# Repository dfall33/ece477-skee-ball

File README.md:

# Electronic Skee Ball Machine

## Overview 

This repository contains the source code for the Electronic Skee Ball machine project. This project was created as a senior capstone design project for Purdue University's ECE47700 
course in Spring 2025. 
This project was created by: 
* **Andrew Cali (*Hardware Lead*)**
* **David Fall (*Team Lead*)**
* **Jennifer Ferguson (*Software Lead*)**
* **Madeline Flanagan (*Systems Lead*)**

all of whom are (or were at the time) computer engineering students at Purdue University. 

## Repository Structure
This repository is divided into numerous discrete sections. 
* **src**: This folder contains the embedded C source code for the project. The software in this directory is the final software that was run on the hardware (specifically, on the STM32F091RCT6 MCU that was used in this project). 
* **micropython**: This directory contains some micropython code that was used during early prototyping done on an ESP32 Feather v2 development board. This development board (or any type of ESP32) was not used in the final design of the project. None of the software in this directory was used in the final design of the project.
* **docs**: This folder contains any and all technical documentation for the project. This includes a product overview, functional specification, etc.
* **hardware**: This folder contains the KiCAD project files for the hardware of the project. This includes the schematic and PCB layout. 
* **packaging**: This folder contains the CAD files for the packaging of the project. This includes the design files for the enclosure and any other packaging components.

## Additional Documentation 

Any and all technical documentation, including a product overview, functional specification, etc., can be found in the `docs` folder in this repository.

## Demonstration Video
A demonstration video of the project can be found at the following link: [Electronic Skee Ball Machine Demonstration Video](https://youtu.be/028JnDdOcIg). This same video is available in MP4 format in the A14 - Project Archive zip file in this repository.

## Hardware Design
The hardware of the project, including the schematic and PCB layout, is designed using KiCAD. The KiCAD project files can be found in the `hardware` folder. 

## Packaging Design 
The packaging for the product hardware and user interface was designed using a variety of softwares. The main components of the packaging design were designed using CAD. Relevant CAD files are contained in the `packaging` folder in this repository. 

Various resources at Purdue University were used to create the packaging. These include but are not limited to university-provided 3D printers and university-owned woodworking tools.

## Reusability 
The software contained in this repository was designed specifically for the hardware of this project. It is not intended for reuse on alternative hardware configurations. However, should one order the exact PCB that was designed for this project and incorporate the components listed in the BOM, the software should work as intended.

## Contact Information
At the time of reading this, it is possible that the team members have graduated from Purdue University, meaning that they may not be reachable at their Purdue email addresses. For any questions or comments, please contact David Fall at his personal email address 
[david.c.fall33@gmail.com](mailto:david.c.fall33@gmail.com).

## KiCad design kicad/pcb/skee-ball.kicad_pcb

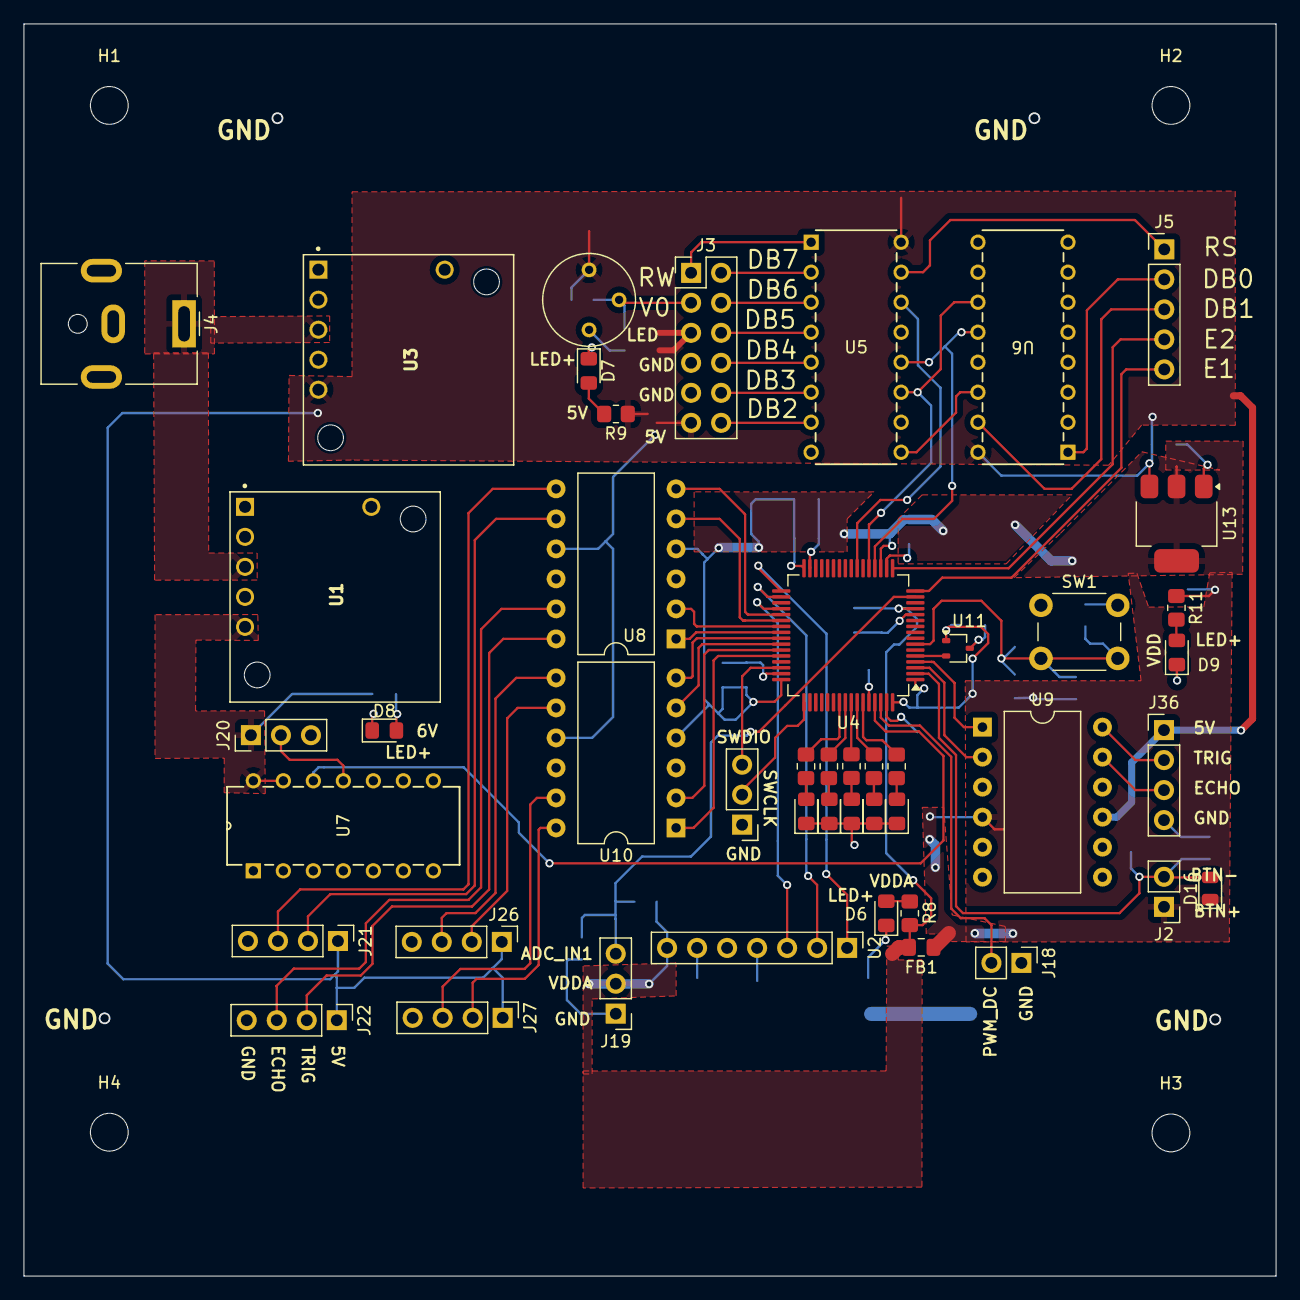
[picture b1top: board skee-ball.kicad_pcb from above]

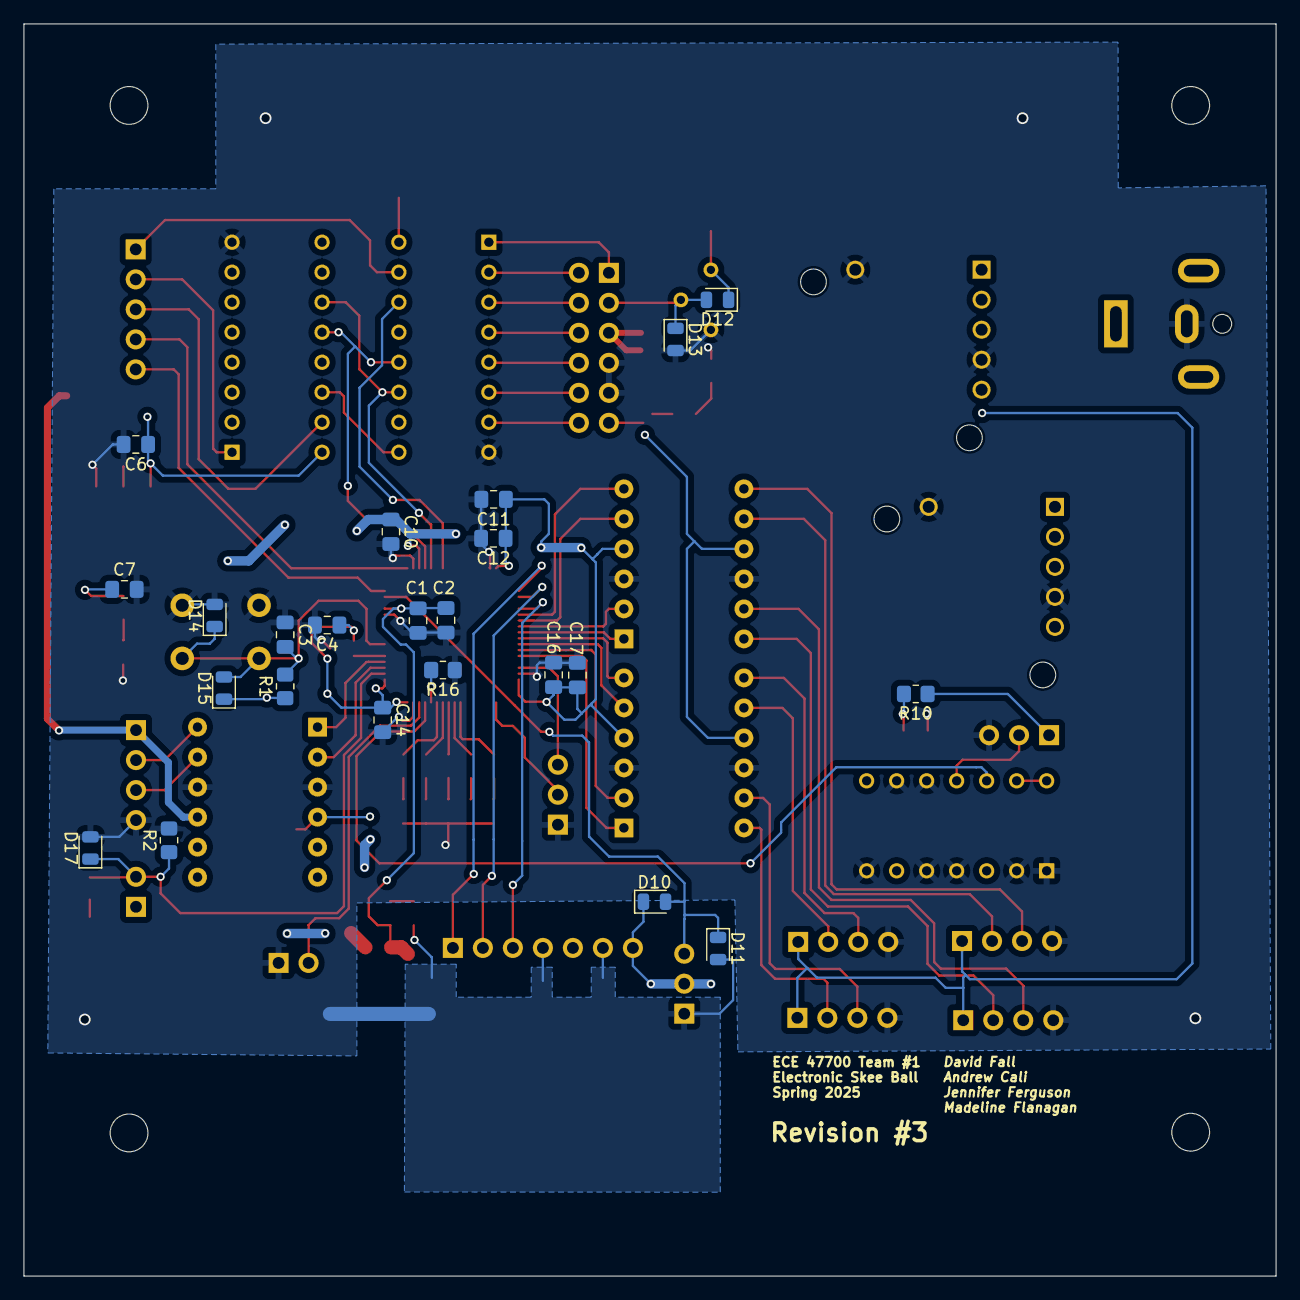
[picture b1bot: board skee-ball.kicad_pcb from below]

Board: 2 copper layers, 106.0 x 106.0 mm, 73 parts (23 on the bottom side), 70 nets.

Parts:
C1: 10nF; C_0805_2012Metric_Pad1.18x1.45mm_HandSolder
C2: 1uF; C_0805_2012Metric_Pad1.18x1.45mm_HandSolder
C3, C4, C6, C10, C12, C14, C16: 100nF; C_0805_2012Metric_Pad1.18x1.45mm_HandSolder
C7: 10uF; C_0805_2012Metric_Pad1.18x1.45mm_HandSolder
C11, C17: 4.7uF; C_0805_2012Metric_Pad1.18x1.45mm_HandSolder
D1, D2, D3, D4, D5, D6, D7, D8, D9: LED; LED_0805_2012Metric_Pad1.15x1.40mm_HandSolder
D10, D11, D12, D13, D14, D15, D16, D17: D_Schottky; D_0805_2012Metric
FB1: FerriteBead; C_0805_2012Metric_Pad1.18x1.45mm_HandSolder
H1, H2, H3, H4: MountingHole; MountingHole_3.2mm_M3
J2: EXTERNAL_BUTTON; PinHeader_1x02_P2.54mm_Vertical
J3: NHD_CONN1; PinHeader_2x06_P2.54mm_Vertical
J4: Barrel_Jack; BarrelJack_CUI_PJ-063AH_Horizontal
J5: NHD_CONN2; PinHeader_1x05_P2.54mm_Vertical
J13: HEADER; PinHeader_1x03_P2.54mm_Vertical
J18: DC_DRIVER; PinHeader_1x02_P2.54mm_Vertical
J19: JOYSTICK; PinHeader_1x03_P2.54mm_Vertical
J20: SERVO; PinHeader_1x03_P2.54mm_Vertical
J21: US0; PinHeader_1x04_P2.54mm_Vertical
J22: US1; PinHeader_1x04_P2.54mm_Vertical
J26: US2; PinHeader_1x04_P2.54mm_Vertical
J27: US3; PinHeader_1x04_P2.54mm_Vertical
J36: US4; PinHeader_1x04_P2.54mm_Vertical
R1, R2: 10k; R_0805_2012Metric_Pad1.20x1.40mm_HandSolder
R3, R4, R5, R6, R7, R8, R11: 150; R_0805_2012Metric_Pad1.20x1.40mm_HandSolder
R9: 200; R_0805_2012Metric_Pad1.20x1.40mm_HandSolder
R10: 300; R_0805_2012Metric_Pad1.20x1.40mm_HandSolder
R16: 2200; R_0805_2012Metric_Pad1.20x1.40mm_HandSolder
RV1: 10k; Potentiometer_Bourns_3339P_Vertical
SW1: SW_Push; SW_PUSH_6mm
U1: D24V22F6; XDCR_12V_2.2A_STEP-DOWN_D24V22F12
U2: MAX98357A; PinHeader_1x07_P2.54mm_Vertical
U3: D24V22F5; XDCR_12V_2.2A_STEP-DOWN_D24V22F12
U4: STM32F091RCTx; LQFP-64_10x10mm_P0.5mm
U5, U6: 74HC595; SOT38-4_NXP
U7: 74LS08; N14
U8, U9, U10: DIP-12_W10.16mm
U11: MAX7375AXR805; SOT-323_SC-70
U13: LD1117S33TR_SOT223; SOT-223-3_TabPin2

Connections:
+5V: C6.1, D12.1 (K), J3.5, J3.11, J21.1, J22.1, J26.1, J27.1, J36.1, R9.1, RV1.1, U3.5 (VOUT), U5.16 (VCC), U6.16 (VCC), U8.9 (HV), U9.9 (HV), U10.9 (HV), U13.3 (VI)
+6V: J20.1, R10.1, U1.5 (VOUT), U7.13, U7.14 (VCC)
+24V: J4.1, U1.3 (VIN), U3.3 (VIN)
/BOOT0: R16.2, U4.60 (PF11)
ADC_IN1: D10.2 (A), D11.1 (K), J19.3, U4.15 (PA1)
BUTTON_IN: D16.2 (A), D17.1 (K), J2.2, R2.1, U4.2 (PC13)
EXTERNAL_CLK: U4.5 (PF0), U11.2 (CLOCK)
GND: C1.2, C2.2, C3.1, C4.2, C6.2, C7.2, C10.2, C11.2, C12.2, C14.2, C16.2, C17.2, D1.1 (K), D2.1 (K), D3.1 (K), D4.1 (K), D5.1 (K), D6.1 (K), D7.1 (K), D8.1 (K), D9.1 (K), D11.2 (A), D13.2 (A), D14.2 (A), D17.2 (A), J3.7, J3.9, J4.2, J13.1, J18.1, J19.1, J20.3, J21.4, J22.4, J26.4, J27.4, J36.4, R2.2, R16.1, RV1.3, SW1.1, U1.4 (GND), U1.6 (GND), U2.4 (GAIN_SLOT), U2.6 (GND), U3.4 (GND), U3.6 (GND), U4.12 (VSSA), U4.18 (VSS), U4.31 (VSS), U4.47 (VSS), U4.63 (VSS), U5.8 (GND), U6.8 (GND), U7.1, U7.2, U7.4, U7.5, U7.7 (GND), U7.9, U7.10, U8.3 (GND), U8.10 (GND), U9.3 (GND), U9.10 (GND), U10.3 (GND), U10.10 (GND), U11.3 (GND), U13.1 (GND)
NHD_DB0: J5.2, U6.1 (QB)
NHD_DB1: J5.3, U6.15 (QA)
NHD_DB2: J3.12, U5.7 (QH)
NHD_DB3: J3.10, U5.6 (QG)
NHD_DB4: J3.8, U5.5 (QF)
NHD_DB5: J3.6, U5.4 (QE)
NHD_DB6: J3.4, U5.3 (QD)
NHD_DB7: J3.2, U5.2 (QC)
NHD_E1: J5.5, U4.16 (PA2)
NHD_E2: J5.4, U4.17 (PA3)
NHD_RS: J5.1, U5.15 (QA)
NHD_RW: J3.1, U5.1 (QB)
NHD_V0: D12.2 (A), D13.1 (K), J3.3, RV1.2
NRST: C3.2, D14.1 (K), D15.2 (A), R1.2, SW1.2, U4.7 (NRST)
unnamed: D1.2 (A), R3.2
unnamed: D2.2 (A), R4.2
unnamed: D3.2 (A), R5.2
unnamed: D4.2 (A), R6.2
unnamed: D5.2 (A), R7.2
unnamed: D6.2 (A), R8.2
unnamed: D7.2 (A), R9.2
unnamed: D8.2 (A), R10.2
unnamed: D9.2 (A), R11.2
PB3: R6.1, U4.55 (PB3)
PB4: R7.1, U4.56 (PB4)
PB5: R3.1, U4.57 (PB5)
PB6: R4.1, U4.58 (PB6)
PB7: R5.1, U4.59 (PB7)
PWM_DC: J18.2, U4.62 (PB9)
PWM_SERVO_3.3: U4.61 (PB8), U7.12
PWM_SERVO_6: J20.2, U7.11
RCLK: U4.20 (PA4), U5.12 (RCLK), U6.12 (RCLK)
SER-CHAIN: U5.9 (QH'), U6.14 (SER)
SPI1-MOSI: U4.23 (PA7), U5.14 (SER)
SPI1-SCK: U4.21 (PA5), U5.11 (SRCLK), U6.11 (SRCLK)
SPI2-MOSI(I2S_SD): U2.3 (DIN), U4.36 (PB15)
SPI2-NSS(I2S_WS): U2.1 (LRCLK), U4.33 (PB12)
SPI2-SCK(I2S_CK): U2.2 (BCLK), U4.34 (PB13)
SWCLK: J13.2, U4.49 (PA14)
SWDIO: J13.3, U4.46 (PA13)
US_ECHO0_3.3: U4.37 (PC6), U8.6 (LV1)
US_ECHO0_5: J21.3, U8.7 (HV1)
US_ECHO1_3.3: U4.39 (PC8), U8.2 (LV3)
US_ECHO1_5: J22.3, U8.11 (HV3)
US_ECHO2_3.3: U4.41 (PA8), U10.6 (LV1)
US_ECHO2_5: J26.3, U10.7 (HV1)
US_ECHO3_3.3: U4.43 (PA10), U10.2 (LV3)
US_ECHO3_5: J27.3, U10.11 (HV3)
US_ECHO4_3.3: U4.3 (PC14), U9.2 (LV3)
US_ECHO4_5: J36.3, U9.11 (HV3)
US_TRIG0_3.3: U4.38 (PC7), U8.5 (LV2)
US_TRIG0_5: J21.2, U8.8 (HV2)
US_TRIG1_3.3: U4.40 (PC9), U8.1 (LV4)
US_TRIG1_5: J22.2, U8.12 (HV4)
US_TRIG2_3.3: U4.42 (PA9), U10.5 (LV2)
US_TRIG2_5: J26.2, U10.8 (HV2)
US_TRIG3_3.3: U4.44 (PA11), U10.1 (LV4)
US_TRIG3_5: J27.2, U10.12 (HV4)
US_TRIG4_3.3: U4.4 (PC15), U9.1 (LV4)
US_TRIG4_5: J36.2, U9.12 (HV4)
VDD: C4.1, C7.1, C10.1, C11.1, C12.1, C14.1, C16.1, C17.1, D15.1 (K), D16.1 (K), FB1.1, J2.1, R1.1, R11.1, U4.1 (VBAT), U4.19 (VDD), U4.32 (VDD), U4.48 (VDDIO2), U4.64 (VDD), U8.4 (LV), U9.4 (LV), U10.4 (LV), U11.1 (V+), U13.2 (VO)
VDDA: C1.1, C2.1, D10.1 (K), FB1.2, J19.2, R8.1, U2.7 (VDD), U4.13 (VDDA)

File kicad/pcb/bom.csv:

"Reference","Value","Datasheet","Footprint","Qty","DNP"
"C1","10nF","~","Capacitor_SMD:C_0805_2012Metric_Pad1.18x1.45mm_HandSolder","1",""
"C3,C6,C10,C12,C14,C16","100nF","~","Capacitor_SMD:C_0805_2012Metric_Pad1.18x1.45mm_HandSolder","6",""
"C2","1uF","~","Capacitor_SMD:C_0805_2012Metric_Pad1.18x1.45mm_HandSolder","1",""
"C11,C17","4.7uF","~","Capacitor_SMD:C_0805_2012Metric_Pad1.18x1.45mm_HandSolder","2",""
"C7","10uF","~","Capacitor_SMD:C_0805_2012Metric_Pad1.18x1.45mm_HandSolder","1",""
"R3,R4,R5,R6,R7,R8,R11","150","~","Resistor_SMD:R_0805_2012Metric_Pad1.20x1.40mm_HandSolder","7",""
"R9","200","~","Resistor_SMD:R_0805_2012Metric_Pad1.20x1.40mm_HandSolder","1",""
"R10","300","~","Resistor_SMD:R_0805_2012Metric_Pad1.20x1.40mm_HandSolder","1",""
"R1,R2","10k","~","Resistor_SMD:R_0805_2012Metric_Pad1.20x1.40mm_HandSolder","2",""
"RV1","10k","~","Potentiometer_THT:Potentiometer_Bourns_3339P_Vertical","1",""
"U5,U6","74HC595","http://www.ti.com/lit/ds/symlink/sn74hc595.pdf","74HC595N:SOT38-4_NXP","2",""
"U7","74LS08","http://www.ti.com/lit/gpn/sn74LS08","SN74LS08N:N14","1",""
"J4","Barrel_Jack","~","Connector_BarrelJack:BarrelJack_CUI_PJ-063AH_Horizontal","1",""
"J5","Conn_01x05","~","Connector_PinHeader_2.54mm:PinHeader_1x05_P2.54mm_Vertical","1",""
"J3","Conn_02x06_Counter_Clockwise","~","Connector_PinHeader_2.54mm:PinHeader_2x06_P2.54mm_Vertical","1",""
"U3","D24V22F5","https://engineering.purdue.edu/477grp1/Files/refs/d24v22f5.pdf","12V_2.2A_STEP-DOWN_D24V22F12:XDCR_12V_2.2A_STEP-DOWN_D24V22F12","1",""
"U1","D24V22F6","https://engineering.purdue.edu/477grp1/Files/refs/d24v22f6.pdf","12V_2.2A_STEP-DOWN_D24V22F12:XDCR_12V_2.2A_STEP-DOWN_D24V22F12","1",""
"J18","DC_DRIVER","~","Connector_PinHeader_2.54mm:PinHeader_1x02_P2.54mm_Vertical","1",""
"J2","EXTERNAL_BUTTON","~","Connector_PinHeader_2.54mm:PinHeader_1x02_P2.54mm_Vertical","1",""
"FB1","FerriteBead","~","Capacitor_SMD:C_0805_2012Metric_Pad1.18x1.45mm_HandSolder","1",""
"J13","HEADER","~","Connector_PinHeader_2.54mm:PinHeader_1x03_P2.54mm_Vertical","1",""
"J19","JOYSTICK","~","Connector_PinHeader_2.54mm:PinHeader_1x03_P2.54mm_Vertical","1",""
"U13","LD1117S33TR_SOT223","http://www.st.com/st-web-ui/static/active/en/resource/techni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","Package_TO_SOT_SMD:SOT-223-3_TabPin2","1",""
"D1,D2,D3,D4,D5,D6,D7,D8,D9","LED","~","LED_SMD:LED_0805_2012Metric_Pad1.15x1.40mm_HandSolder","9",""
"U2","MAX98357A","https://www.analog.com/media/en/technical-documentation/data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","max98357A:MAX98347A_ADAFRUIT_I2S_BREAKOUT","1",""
"J20","SERVO","~","Connector_PinHeader_2.54mm:PinHeader_1x03_P2.54mm_Vertical","1",""
"U4","STM32F091RCTx","https://engineering.purdue.edu/477grp1/Files/refs/stm32f091cc.pdf","Package_QFP:LQFP-64_10x10mm_P0.5mm","1",""
"SW1","SW_Push","~","Button_Switch_THT:SW_PUSH_6mm","1",""
"J21","US0","~","Connector_PinHeader_2.54mm:PinHeader_1x04_P2.54mm_Vertical","1",""
"J22","US1","~","Connector_PinHeader_2.54mm:PinHeader_1x04_P2.54mm_Vertical","1",""
"J26","US2","~","Connector_PinHeader_2.54mm:PinHeader_1x04_P2.54mm_Vertical","1",""
"J27","US3","~","Connector_PinHeader_2.54mm:PinHeader_1x04_P2.54mm_Vertical","1",""
"J36","US4","~","Connector_PinHeader_2.54mm:PinHeader_1x04_P2.54mm_Vertical","1",""
"U8,U9,U10","~","","Package_DIP:DIP-12_W10.16mm","3",""

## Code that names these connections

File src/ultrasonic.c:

#include "ultrasonic.h"
#include "stm32f0xx.h"

void micro_wait(int);

volatile int pulse_timed_out = 0;
volatile int search_timed_out = 0;

volatile int timeout_counter = 0;

extern void led_high(int index);
extern void led_low(int index);

extern void spi_write_str(char *, int);

void time_out_pulse()
{
    pulse_timed_out = 1;
}

void time_out_hcsr04_search()
{
    spi_write_str("Time out!", 3); // Display timeout message on the display
    search_timed_out = 1;
}

uint8_t read_hcsr04(int index)
{

    switch (index)
    {
    // first sensor echo=PC6, trigger=PC7
    case 0:
        return wait_for_echo(
            GPIOC,      // port,
            GPIO_IDR_6, // idr pin
            GPIO_ODR_7  // odr pin
        );

    // second sensor echo=PC8, trigger=PC9
    case 1:
        return wait_for_echo(
            GPIOC,      // port,
            GPIO_IDR_8, // idr pin
            GPIO_ODR_9  // odr pin
        );

    // third sensor echo=PA8, trigger=PA9
    case 2:
        return wait_for_echo(
            GPIOA,      // port,
            GPIO_IDR_8, // idr pin
            GPIO_ODR_9  // odr pin
        );

    // third sensor echo=PA10, trigger=PA11
    case 3:
        return wait_for_echo(
            GPIOA,       // port,
            GPIO_IDR_10, // idr pin
            GPIO_ODR_11  // odr pin
        );

    // fifth sensor echo = PC14, trigger = PC15
    case 4:
        return wait_for_echo(
            GPIOC,       // port,
            GPIO_IDR_14, // idr pin
            GPIO_ODR_15  // odr pin
        );
    }

    return 0; 
}

void start_hcsr04_pulse_timer()
{
    TIM14->CNT = 0;
    TIM14->DIER |= TIM_DIER_UIE;
    TIM14->CR1 |= TIM_CR1_CEN;
}

void stop_hcsr04_pulse_timer()
{
    TIM14->CR1 &= ~TIM_CR1_CEN;
    TIM14->DIER &= ~TIM_DIER_UIE;
}

void start_hcsr04_search_timer()
{
    NVIC_ClearPendingIRQ(TIM15_IRQn); // Clear any pending interrupt for TIM15 before starting it
    TIM15->CNT = 0;
    TIM15->DIER |= TIM_DIER_UIE;
    TIM15->SR &= ~TIM_SR_UIF; // clear any pending update interrupt flag
    TIM15->CR1 |= TIM_CR1_CEN;
    NVIC_EnableIRQ(TIM15_IRQn); // Enable the interrupt for TIM15 to handle timeouts
    timeout_counter = 0;
}

void stop_hcsr04_search_timer()
{
    timeout_counter = 0;
    TIM15->CR1 &= ~TIM_CR1_CEN;
    TIM15->DIER &= ~TIM_DIER_UIE;
    NVIC_DisableIRQ(TIM15_IRQn); // Disable the interrupt for TIM15 to prevent further timeouts
}

void send_hcsr04_pulse(GPIO_TypeDef *port, uint32_t pin)
{

    port->ODR |= pin;
    micro_wait(10);
    port->ODR &= ~pin;
}

uint8_t wait_for_echo(GPIO_TypeDef *port, volatile uint32_t idr_pin, uint32_t odr_pin)
{
    pulse_timed_out = 0;
    start_hcsr04_pulse_timer();

    volatile int start = 0;
    volatile uint8_t duration = 0;
    send_hcsr04_pulse(port, odr_pin);
    int offset = TIM14->CNT;
    while (!pulse_timed_out || start)
    {
        if ((port->IDR & idr_pin) && start == 0)
        {
            start = TIM14->CNT;
        }

        if (!(port->IDR & idr_pin) && start != 0)
        {
            duration = TIM14->CNT - start - offset;
            stop_hcsr04_pulse_timer();
            pulse_timed_out = 0;
            break;
        }

    }

    stop_hcsr04_pulse_timer();
    if (pulse_timed_out)
    {
        return 0; 
    }
    else if (duration)
    {

        return duration > 0 && duration < 150 ? duration : 0 ; 
    }
    else
    {
        return 0; 
    }
}

int search_hcsr04(int stability_count)
{
    search_timed_out = 0;
    start_hcsr04_search_timer();
    search_timed_out = 0;

    volatile int count = 0;
    uint8_t duration = 0;
    while (!search_timed_out)
    {
        for (int i = 0; i < 3; i++)
        {
            count++;

            duration = read_hcsr04(i);
            if (duration > 10 && duration < 80 && count >= stability_count)
            {
                stop_hcsr04_search_timer();

                // char buf[20] ; 
                // sprintf(buf, "Sensor %d: %d", i, duration);
                // spi_write_str(buf, 1);

                return i;
            }

            micro_wait(HCSR04_GAP_TIME_US);
        }
    }

    stop_hcsr04_search_timer();
    return BALL_NOT_FOUND;
}

int test_sensor(int8_t index)
{

    int duration = read_hcsr04(index);
    if (duration > 0)
    {
        // Successfully received an echo from the sensor
        return duration;
    }
    else
    {
        // No echo received from the sensor
        return 0;
    }
}

void setup_ultrasonic_ports()
{

    // This function is used to setup the ultrasonic sensor ports for input and output

    // Enable clock for GPIOC and GPIOA (assuming sensors are connected to these ports)
    RCC->AHBENR |= RCC_AHBENR_GPIOCEN | RCC_AHBENR_GPIOAEN;

    // reset all (puts into input mode)
    GPIOC->MODER &= ~(
        GPIO_MODER_MODER6 |
        GPIO_MODER_MODER7 |
        GPIO_MODER_MODER8 |
        GPIO_MODER_MODER9 |
        GPIO_MODER_MODER14 |
        GPIO_MODER_MODER15);

    GPIOA->MODER &= ~(
        GPIO_MODER_MODER8 |
        GPIO_MODER_MODER9 |
        GPIO_MODER_MODER10 |
        GPIO_MODER_MODER11);

    // configure trigger pins for echo mode

    GPIOC->MODER |= (GPIO_MODER_MODER7_0 |
                     GPIO_MODER_MODER9_0 |
                     GPIO_MODER_MODER15_0);

    GPIOA->MODER |= (GPIO_MODER_MODER9_0 |
                     GPIO_MODER_MODER11_0); // PA9 and PA11 are used for the third and fourth sensors respectively
}

void setup_tim15()
{
    RCC->APB2ENR |= RCC_APB2ENR_TIM15EN;
    TIM15->PSC = 480 - 1;   // 48 MHz / 48000 = 1 kHz
    TIM15->ARR = 10000 - 1; // 1 kHz / 10000 = 0.1 Hz (10 seconds)
    // don't enable the timer yet, because we want to start it when we start the ultrasonic sensor
}

void TIM15_IRQHandler(void)
{
    TIM15->SR &= ~TIM_SR_UIF;

    if (timeout_counter < 100)
        timeout_counter++;
    else
        time_out_hcsr04_search();
}

void setup_tim14()
{

    // enable clock to TIM14
    RCC->APB1ENR |= RCC_APB1ENR_TIM14EN;
    TIM14->PSC = 48 - 1; // 48 MHz / 48 = 1 MHz
    TIM14->ARR = 500;  // 1 MHz / 30000 = 33.33 Hz

    // enable the interrupt on timer overflow
    TIM14->DIER |= TIM_DIER_UIE;

    // enable the interrupt in the NVIC
    NVIC_EnableIRQ(TIM14_IRQn);

    // don't enable the timer yet, because we want to start it when we start the ultrasonic sensor
}

void TIM14_IRQHandler(void)
{
    TIM14->SR &= ~TIM_SR_UIF;
    time_out_pulse();
    led_high(2); 
}

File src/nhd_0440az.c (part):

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    while ((SPI1->SR & SPI_SR_TXE) == 0)
        ;

    // Set the RCLK pin high
    GPIOA->ODR |= GPIO_ODR_4;
    // wait for a short time
    micro_wait(1);

    // Set the RCLK pin low
    GPIOA->ODR &= ~GPIO_ODR_4;
    // wait for a short time
    micro_wait(1);
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    while ((SPI1->SR & SPI_SR_TXE) == 0)
        ;
    SPI1->DR = data; // Load the data into the SPI data register
    pulse_rclk();    // Pulse the RCLK pin to latch the data
}

void spi_char(char character, uint8_t line_pair)
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    GPIOA->AFR[0] &= ~(GPIO_AFRL_AFRL7 | GPIO_AFRL_AFRL5);
    GPIOA->AFR[1] &= ~(GPIO_AFRH_AFRH7);

    // configure NSS, SCK, MOSI signals of SPI1 to pins PA15, PA5, PA7, respectively
    // set the alternate function bits for the pins
    GPIOA->AFR[0] |= (0x0 << GPIO_AFRL_AFRL7_Pos) | (0x0 << GPIO_AFRL_AFRL5_Pos);
    GPIOA->AFR[1] |= (0x0 << GPIO_AFRH_AFRH7_Pos);
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    RCC->AHBENR |= RCC_AHBENR_GPIOAEN; // Enable clock for GPIOA

    // Set GPIOA2 and GPIOA3 as output for NHD E1 and NHD E2 respectively
    GPIOA->MODER &= ~(GPIO_MODER_MODER2 | GPIO_MODER_MODER3); // Clear the mode bits for PA2 and PA3
    GPIOA->MODER |= GPIO_MODER_MODER2_0 | GPIO_MODER_MODER3_0; // Set PA2 and PA3 to output mode

    // Set GPIOA4 as output for RCLK (latch clock)
    GPIOA->MODER &= ~(GPIO_MODER_MODER4); // Clear the mode bits for PA4
    GPIOA->MODER |= GPIO_MODER_MODER4_0; // Set PA4 to output mode
}

void setup_display()
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
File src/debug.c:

#include "debug.h"

extern void micro_wait(int); 

void setup_debug_ports()
{

    // LEDs are on PB3-PB7, so enable clock to GPIOB
    RCC->AHBENR |= RCC_AHBENR_GPIOBEN;

    // Set PB3-PB7 to output mode
    GPIOB->MODER &= ~(
        GPIO_MODER_MODER3 |
        GPIO_MODER_MODER4 |
        GPIO_MODER_MODER5 |
        GPIO_MODER_MODER6); 
        // GPIO_MODER_MODER6 |
        // GPIO_MODER_MODER7);

    GPIOB->MODER |= (GPIO_MODER_MODER3_0 |
                     GPIO_MODER_MODER4_0 |
                     GPIO_MODER_MODER5_0 |
                     GPIO_MODER_MODER6_0);
                    //  GPIO_MODER_MODER6_0 |
                    //  GPIO_MODER_MODER7_0);
}

void led_high(int8_t index)
{
    if (index < 0 || index > 4)
        return;

    switch (index)
    {

    // for GPIOB3
    case 0:
        GPIOB->BSRR |= GPIO_BSRR_BS_3;
        break;

    // for GPIOB4
    case 1:
        GPIOB->BSRR |= GPIO_BSRR_BS_4;
        break;

    // for GPIOB5
    case 2:
        GPIOB->BSRR |= GPIO_BSRR_BS_5;
        break;

    // for GPIOB6
    case 3:
        GPIOB->BSRR |= GPIO_BSRR_BS_6;
        break;

    }
}

void led_low(int8_t index)
{
    if (index < 0 || index > 4)
        return;

    switch (index)
    {
        case 0:
            GPIOB->BSRR |= GPIO_BSRR_BR_3; // Set PB3 low
            break;
        case 1:
            GPIOB->BSRR |= GPIO_BSRR_BR_4; // Set PB4 low
            break;
        case 2:
            GPIOB->BSRR |= GPIO_BSRR_BR_5; // Set PB5 low
            break;
        case 3:
            GPIOB->BSRR |= GPIO_BSRR_BR_6; // Set PB6 low
            break;
    }
}

void led_off()
{
    
    // Turn off all LEDs by setting all bits low
    GPIOB->BSRR |= (GPIO_BSRR_BR_3 | // Set PB3 low
                    GPIO_BSRR_BR_4 | // Set PB4 low
                    GPIO_BSRR_BR_5 | // Set PB5 low
                    GPIO_BSRR_BR_6); // Set PB6 low
                                     // GPIO_BSRR_BR_6 |  // Set PB6 low
                                     // GPIO_BSRR_BR_7);  // Set PB7 low
    // Alternatively, you could loop through each LED and call led_low(index) for each one.
}


void flash_leds()
{

    led_off(); 
    micro_wait(1000000); 

    led_high(0); // Turn on LED at index 0 (PB3)
    micro_wait(100000); // Wait for 100ms
    
    led_high(1); // Turn on LED at index 1 (PB4)
    micro_wait(100000); // Wait for 100ms

    led_high(2); // Turn on LED at index 2 (PB5)
    micro_wait(100000); // Wait for 100ms

    led_high(3); // Turn on LED at index 3 (PB6)
    micro_wait(100000); // Wait for 100ms

    led_low(0); // Turn off LED at index 0 (PB3)
    micro_wait(100000); // Wait for 100ms

    led_low(1); // Turn off LED at index 1 (PB4)
    micro_wait(100000); // Wait for 100ms

    led_low(2); // Turn off LED at index 2 (PB5)
    micro_wait(100000); // Wait for 100ms

    led_low(3); // Turn off LED at index 3 (PB6)
    micro_wait(100000); // Wait for 100ms
}

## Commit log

2025-01-22 prototype push button press duration
2025-01-23 prototype oled display
2025-01-23 add soc1602a class
2025-01-26 prototype I2S usage
2025-01-29 Create ultrasonic_prototyping.py
    prototype ultrasonic sensor hc-sr04
2025-01-30 test ultrasonic mux
2025-02-02 add progress bar
2025-02-02 update game state transitions
2025-02-13 create micropython archive
2025-02-13 init pio env
2025-02-14 begin hcsr04 migration
2025-02-16 begin schematic and pcb layout
2025-02-17 add to pcb schematic
2025-02-18 add ultrasonic module
2025-02-18 add comments
2025-02-19 added external parts schematic project
    couldn't find symbols for most components, so will need to create custom ones if necessary
2025-02-19 add AND gate to pcb schematic
2025-02-19 add ultrasonic, speaker, nhd
2025-02-19 add timer labels to pwm signals
2025-02-19 add push button module
2025-02-19 fix spi1 mosi pin assignment
2025-02-20 add LDOs to pcb schematic
2025-02-20 update cap values for stm supply voltage
2025-02-21 start 4line prototyping
2025-02-21 fix nhd enable signal label on schematic
2025-02-21 added header connection pins
2025-02-21 add nhd display module
2025-02-21 add debugging circuitry to schematic
2025-02-23 added pcb layout
2025-02-25 begin routing on pcb
2025-02-25 add decoupling circuitry for mcu power
2025-02-26 added ground plane and some via connections
2025-02-26 update pcb
2025-02-27 add level shifter
2025-02-27 transition to level shifters
2025-02-27 add new connector footprints
2025-02-28 add first successful routing
2025-02-28 finish routing
2025-02-28 add level shifter symbol
2025-03-01 added power zones and started debugging DRC
2025-03-01 eliminate all drc errors
2025-03-02 finish pcb silkscreen
2025-03-02 generate gerber and bom
2025-03-02 add gerbers
2025-03-02 minor changes
2025-03-02 remove unneccesary 5v rail
2025-03-03 minor changes to schematic
2025-03-03 reposition pcb mounting holes
2025-03-03 update silkscreen
2025-03-05 created version 8.0 of pcb
2025-03-05 only one drc error left
2025-03-05 fix pcb dimensions
2025-03-05 reorganize schematic and fix max98357a pins
2025-03-05 update silk screen
2025-03-05 update revision number and sheet details
2025-03-05 update schematic sheet details
2025-03-05 reshape power planes
2025-03-05 add large vias for debugging
2025-03-05 fix analog ground plane connection:
2025-03-11 set up game state machine
2025-03-11 complete game state machine skeleeton
2025-03-11 add sound playing to game
2025-03-11 fix acute angles and minor decoupling cap issues
2025-03-11 move game.c, game.h to src/
2025-03-11 add display function calls to game
2025-03-12 maddie using git
2025-03-12 add esd protection to pcb
2025-03-12 added motor control file
2025-03-12 MF using git again
2025-03-12 pcb revisions before approval
2025-03-13 add esd protection diodes
2025-03-24 update game software
2025-03-24 update ultrasonic sensor ports
2025-03-24 add support for debugging leds
2025-03-25 update state transitions to be non-blocking
2025-03-30 minor changes for pcb software
2025-03-31 add progress bar functionality
2025-03-31 fix issue with sound replayability
2025-03-31 fix pulse width
2025-04-01 fixed servo
2025-04-01 fix issue with joystick update merge
2025-04-01 make display clear line before writing
2025-04-01 fix bug in ultrasonic timeouts
2025-04-01 add game over and final score text
2025-04-03 update button port for flywiring
2025-04-04 clean up comments and unused code
2025-04-04 fix ultrasonic timeout bug
2025-04-04 game software working
2025-04-05 change schematic label from oled to lcd
2025-04-07 make ultrasonic sensors more sensitive
2025-04-10 sensors working with ball drop
2025-04-10 fix servo initial angle and upper and lower bounds
2025-04-11 minor changes before demo
2025-04-11 software used in demo
2025-04-22 add readme and docs/
2025-04-22 add cad files to packaging
2025-04-22 add kicad archive
2025-05-01 add project archive
2025-05-09 add project video link to README
